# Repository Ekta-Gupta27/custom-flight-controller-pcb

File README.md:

# Custom Flight Controller PCB

A custom-designed flight controller PCB developed for embedded flight-control applications, integrating a high-performance STM32 MCU, multiple inertial and pressure sensors, CAN communication, external flash memory, power management, and dedicated FMU/IO interfaces.

The PCB and schematic were designed using **KiCad 9.0.7**.

---

## 📌 Project Overview

This project focuses on the design and development of a custom flight controller PCB with dedicated interfaces for sensors, communication peripherals, power, debugging, telemetry, PWM outputs, and RC input/output.

The design is divided into multiple functional sections:

- Main Flight Management Unit (FMU)
- IO controller
- IMU and pressure sensing
- CAN communication
- USB connectivity
- External SPI flash memory
- Power regulation
- Telemetry interfaces
- PWM and RC interfaces
- Debug/programming interfaces

---

## ✨ Key Features

- Custom PCB designed from schematic to board layout
- STM32F765VITx main flight controller MCU
- STM32F103CBTx dedicated IO controller
- Multiple onboard sensors
- CAN communication interface
- USB OTG interface
- External SPI flash memory
- Multiple UART interfaces
- I2C and SPI interfaces
- PWM output interface
- SBUS and PPM interfaces
- Debug/programming interface
- Dedicated GPS and telemetry connectors
- Onboard status/safety LEDs
- 3.3 V and 5 V power domains
- Multi-layer PCB layout
- Manufacturing-ready Gerber and drill files

---

## 🧠 Hardware Architecture

### Main Flight Controller

The primary processing unit is an **STM32F765VITx**.

The MCU provides the main processing and peripheral interfaces for the flight-control system, including:

- SPI
- I2C
- UART
- CAN
- Timer/PWM channels
- SWD debugging
- External GPIO

### IO Controller

A dedicated **STM32F103CBTx** is used for the IO section of the design.

The IO controller provides interfaces for:

- SBUS
- PPM
- PWM
- RC input/output
- Safety signals
- Status LEDs
- Debugging
- Additional UART interfaces

---

## 📡 Sensors

The design incorporates multiple sensors:

### ICM-42688-P

6-axis inertial measurement sensor connected through SPI.

### BMI270

6-axis inertial sensor with dedicated interrupt and SPI connections.

### ICP-20100

Pressure sensor connected through the I2C interface.

### BMM150

Magnetic sensor connected through the I2C interface.

---

## 🔌 Communication Interfaces

### CAN

CAN communication is implemented using the **SN65HVD230** transceiver with dedicated CANH and CANL connections and protection circuitry.

### USB

A USB OTG interface is provided along with USB ESD protection using **USBLC6-2P6**.

### UART / Telemetry

Dedicated connectors are provided for:

- TELEM1
- TELEM2
- TELEM3
- UART/I2C interface
- GPS
- FMU communication

### I2C

Multiple I2C buses are available for sensor and peripheral communication.

### SPI

Multiple SPI buses are routed to sensors, flash memory, and external interfaces.

---

## 💾 External Flash Memory

The board includes external SPI flash memory:

**W25Q128JVS**

The flash device is connected to the main MCU through SPI with a dedicated chip-select signal.

---

## ⚡ Power Management

The PCB contains dedicated power regulation and filtering circuitry for the different system power domains.

The design includes:

- 5 V input
- 3.3 V regulation
- USB 5 V input
- External 3.3 V supply
- Decoupling capacitors
- Ferrite filtering
- Power indication circuitry

The schematic includes regulators such as:

- LM1117DT-3.3
- TLV75733PDBVR

---

## 🎛️ Interfaces & Connectors

| Interface | Purpose |
|---|---|
| GPS_PORT | GPS connectivity |
| POWER | Power input |
| TELEM1 | Telemetry |
| TELEM2 | Telemetry |
| TELEM3 | Telemetry |
| CAN_CONN | CAN communication |
| USB_OTG | USB connectivity |
| DEBUG | Debug/programming |
| SPI_PORT | External SPI interface |
| I2C_PORT | External I2C interface |
| UART_I2CB | UART/I2C interface |
| FMU_PWM | PWM outputs |
| IO_PWM | IO PWM interface |
| SBUS_PORT | SBUS interface |
| SBUS_IN | SBUS input |
| PPM_PORT | PPM input |
| IO_DEBUG | IO debugging |

---

# 🖥️ PCB Design

## 3D View – Top

## 3D View – Bottom

## PCB Layout

---

# 📐 Schematic

The complete schematic is provided as a multi-page KiCad schematic covering:

1. FMU / MCU power and peripherals
2. USB and CAN
3. IMU and sensor interfaces
4. IO controller
5. Safety, RC and PWM interfaces

The PDF version is available in:

`docs/schematic.pdf`

---

# 🏭 Manufacturing Files

The `gerbers/` directory contains the manufacturing outputs generated from KiCad, including:

- Front and back copper
- Inner copper layers
- Front and back solder mask
- Front and back silkscreen
- Paste layers
- Board outline
- Drill files
- Gerber job file

These files can be supplied to a PCB manufacturer for fabrication.

---

# 📦 Bill of Materials

A Bill of Materials generated from the KiCad schematic is included in:

`manufacturing/BOM.csv`

The BOM contains information such as:

- Reference designators
- Component quantity
- Component value
- PCB footprint
- Datasheet information
- BOM exclusion fields

---

# 📁 Repository Structure

```text
Custom-FC-RAT/
│
├── README.md
├── custom_fc_rat.kicad_pro
│
├── schematic/
│   └── custom_fc_rat.kicad_sch
│
├── pcb/
│   └── custom_fc_rat.kicad_pcb
│
├── gerbers/
│   ├── *.gbl
│   ├── *.gtl
│   ├── *.gbs
│   ├── *.gts
│   ├── *.gbo
│   ├── *.gto
│   ├── *.gm1
│   ├── *.g1
│   ├── *.g2
│   ├── *.g3
│   ├── *.g4
│   ├── *.drl
│   └── *.gbrjob
│
├── manufacturing/
│   └── BOM.csv
│
├── images/
│   ├── pcb_3d_top.png
│   ├── pcb_3d_bottom.png
│   └── pcb_layout.png
│
└── docs/
    └── schematic.pdf
```

---

# 🛠️ Design Tools

| Tool | Purpose |
|---|---|
| KiCad 9.0.7 | Schematic & PCB design |
| KiCad 3D Viewer | PCB visualization |
| KiCad Gerber Generator | Manufacturing file generation |

---

# 🚀 Future Improvements

Possible future development includes:

- Hardware validation and bring-up documentation
- Flight-controller firmware integration
- Sensor calibration and validation
- Power integrity testing
- Communication interface testing
- EMI/EMC validation
- Flight testing
- PCB revisions based on hardware testing

---

# 📄 Documentation

The editable KiCad design files and schematic PDF are included so that the hardware design can be inspected and further developed.

---

# 👩‍💻 Author

**Ekta Gupta**

Custom PCB / Flight Controller Design Project

---

## ⭐ Project Status

**Hardware Design Completed**

Schematic, PCB layout, 3D visualization, BOM, and manufacturing files are included in this repository.

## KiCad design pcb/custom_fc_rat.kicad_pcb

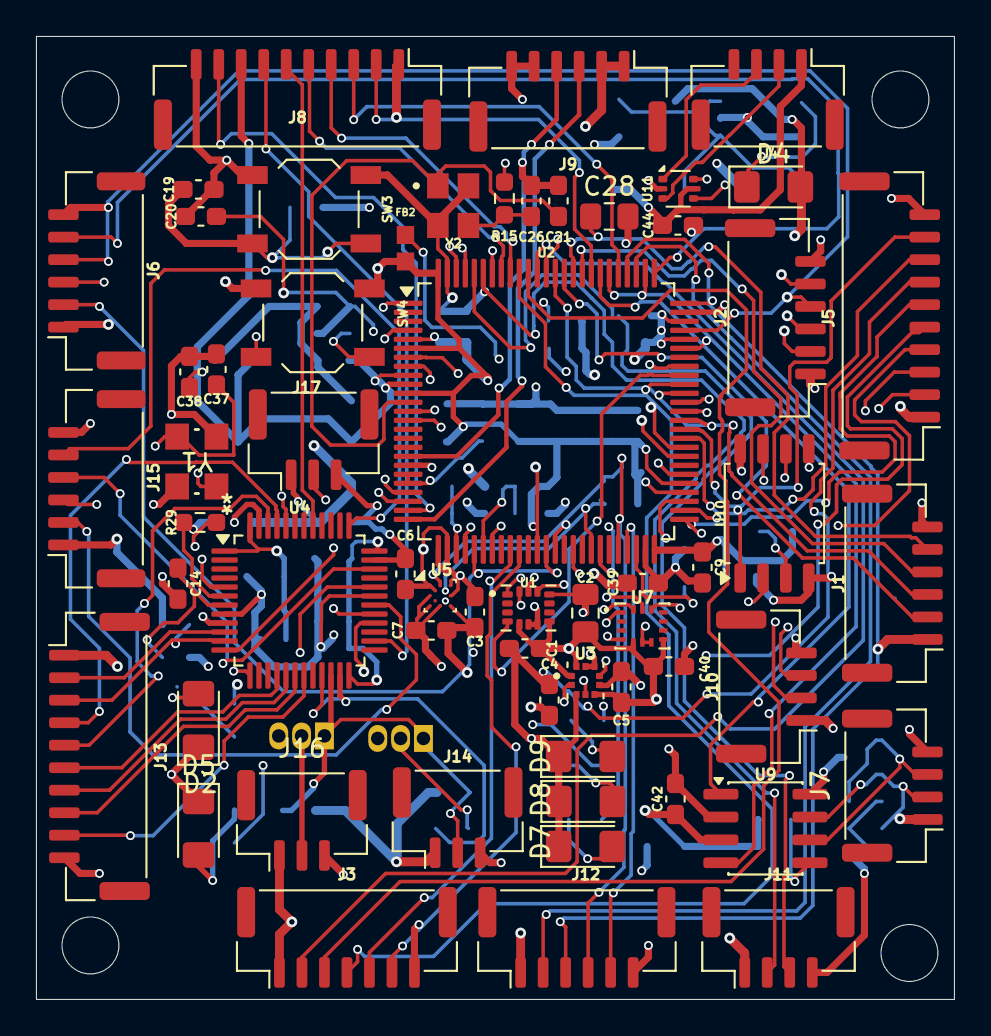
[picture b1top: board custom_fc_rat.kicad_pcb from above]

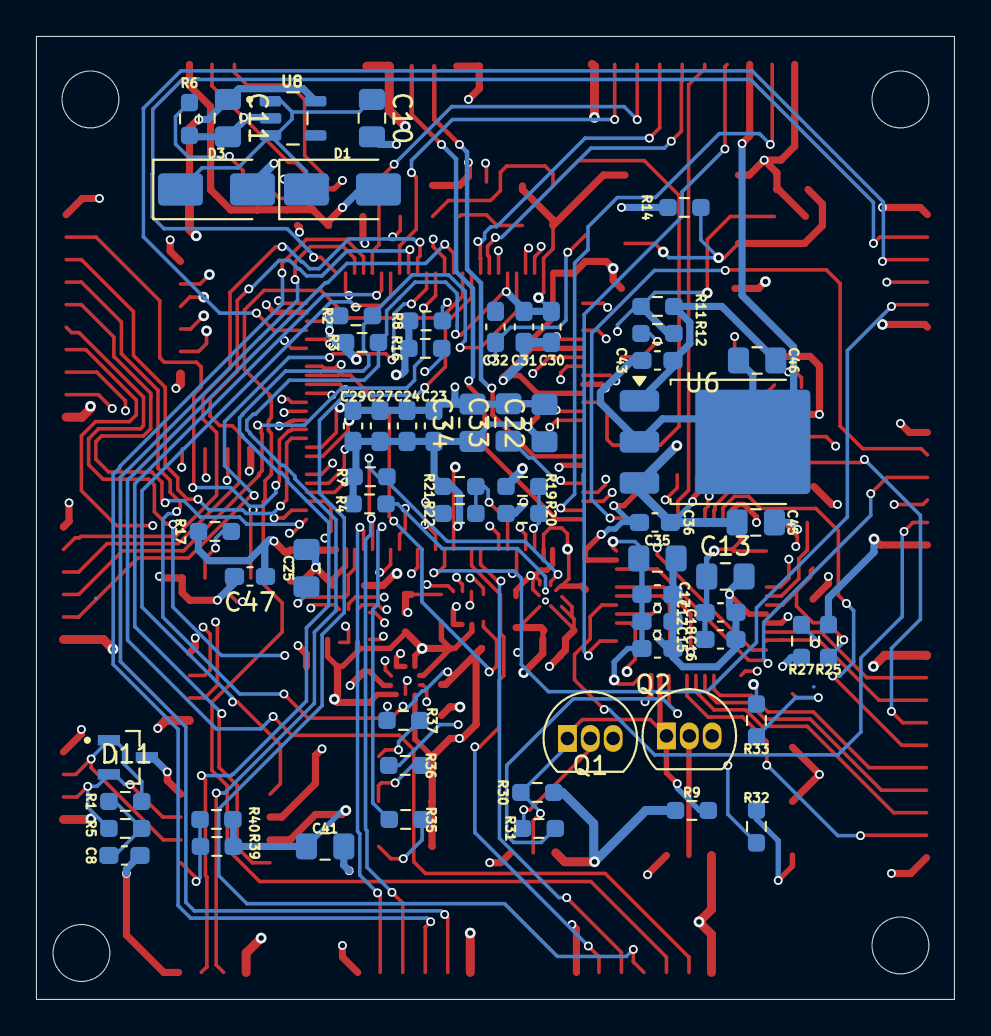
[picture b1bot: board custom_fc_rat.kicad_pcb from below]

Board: 6 copper layers, 51.0 x 53.5 mm, 122 parts (63 on the bottom side), 121 nets.

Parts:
C1, C4, C5, C6, C7, C9, C12, C14, C15, C16, C17, C18, C19, C20, C23, C24, C27, C29, C30, C31, C32, C36, C39, C40, C42, C43, C44: 0.1u; C_0603_1608Metric_Pad1.08x0.95mm_HandSolder
C2, C10, C11: 2.2u; C_0805_2012Metric_Pad1.18x1.45mm_HandSolder
C3: 10n; C_0603_1608Metric_Pad1.08x0.95mm_HandSolder
C8: 4.7n; C_0603_1608Metric_Pad1.08x0.95mm_HandSolder
C13, C33, C34, C41: 1u; C_0805_2012Metric_Pad1.18x1.45mm_HandSolder
C21, C26: 8pF; C_0603_1608Metric_Pad1.08x0.95mm_HandSolder
C22, C35, C45, C46: 10u; C_0805_2012Metric_Pad1.18x1.45mm_HandSolder
C25, C28: 2u2; C_0805_2012Metric_Pad1.18x1.45mm_HandSolder
C37, C38: 18pF; C_0603_1608Metric_Pad1.08x0.95mm_HandSolder
C47: 1u; C_0603_1608Metric_Pad1.08x0.95mm_HandSolder
D1, D3: SS34; D_SMA
D2, D4, D5, D7, D8, D9: LED; LED_1206_3216Metric_Pad1.42x1.75mm_HandSolder
D11: ESD2CANFD24DBZRQ1; SOT95P237X112-3N
FB2: FerriteBead; BEADC1608X95N
J1: TELEM1; JST_GH_BM06B-GHS-TBT_1x06-1MP_P1.25mm_Vertical
J2: TELEM2; JST_GH_BM06B-GHS-TBT_1x06-1MP_P1.25mm_Vertical
J3: SPI_PORT; JST_GH_BM07B-GHS-TBT_1x07-1MP_P1.25mm_Vertical
J4: USB_OTG; JST_GH_BM04B-GHS-TBT_1x04-1MP_P1.25mm_Vertical
J5: FMU_PWM; JST_GH_BM10B-GHS-TBT_1x10-1MP_P1.25mm_Vertical
J6: DEBUG; JST_GH_SM06B-GHS-TB_1x06-1MP_P1.25mm_Horizontal
J7: CAN_CONN; JST_GH_BM04B-GHS-TBT_1x04-1MP_P1.25mm_Vertical
J8: GPS_PORT; JST_GH_BM10B-GHS-TBT_1x10-1MP_P1.25mm_Vertical
J9: POWER; JST_GH_BM06B-GHS-TBT_1x06-1MP_P1.25mm_Vertical
J10: TELEM3; JST_GH_BM04B-GHS-TBT_1x04-1MP_P1.25mm_Vertical
J11: I2C_PORT; JST_GH_BM04B-GHS-TBT_1x04-1MP_P1.25mm_Vertical
J12: UART_I2CB; JST_GH_BM06B-GHS-TBT_1x06-1MP_P1.25mm_Vertical
J13: IO_PWM; JST_GH_BM10B-GHS-TBT_1x10-1MP_P1.25mm_Vertical
J14: SBUS_PORT; JST_GH_BM03B-GHS-TBT_1x03-1MP_P1.25mm_Vertical
J15: IO_DEBUG; JST_GH_SM06B-GHS-TB_1x06-1MP_P1.25mm_Horizontal
J16: SBUS_IN; JST_GH_BM03B-GHS-TBT_1x03-1MP_P1.25mm_Vertical
J17: PPM_PORT; JST_GH_BM03B-GHS-TBT_1x03-1MP_P1.25mm_Vertical
Q1, Q2: BC547; TO-92_Inline
R1, R5: 60R; R_0603_1608Metric_Pad0.98x0.95mm_HandSolder
R2, R3, R4, R7, R8, R16, R39, R40: 4K7; R_0603_1608Metric_Pad0.98x0.95mm_HandSolder
R6: 1k5; R_0603_1608Metric_Pad0.98x0.95mm_HandSolder
R9, R30: 10k; R_0603_1608Metric_Pad0.98x0.95mm_HandSolder
R11, R14, R17, R25, R27: 10K; R_0603_1608Metric_Pad0.98x0.95mm_HandSolder
R12: 22R; R_0603_1608Metric_Pad0.98x0.95mm_HandSolder
R15: 47R; R_0603_1608Metric_Pad0.98x0.95mm_HandSolder
R19, R20, R21, R22: 5K1; R_0603_1608Metric_Pad0.98x0.95mm_HandSolder
R29: 150R; R_0603_1608Metric_Pad0.98x0.95mm_HandSolder
R31: 4.7k; R_0603_1608Metric_Pad0.98x0.95mm_HandSolder
R32, R33, R35, R36, R37: 220R; R_0603_1608Metric_Pad0.98x0.95mm_HandSolder
SW3, SW4: SW_Push; SW_SPST_TL3342
U1: ICM-42688-P; PQFN50P300X250X97-14N
U2: STM32F765VITx; LQFP-100_14x14mm_P0.5mm
U3: ICP-20100; PQFN50P200X200X85-10N
U4: STM32F103CBTx; LQFP-48_7x7mm_P0.5mm
U5: BMM150; WLCSP-12_1.56x1.56mm_P0.4mm
U6: LM1117DT-3.3; TO-252-3_TabPin2
U7: BMI270; XDCR_BMI270
U8: TLV75733PDBVR; SOT95P280X145-5N
U9: SN65HVD230; SOIC-8_3.9x4.9mm_P1.27mm
U10: W25Q128JVS; SOIC-8_5.3x5.3mm_P1.27mm
U11: USBLC6-2P6; SOT-666
Y1: Crystal_GND24; YSX321SL_YXC
Y2: Crystal_GND24; OSC_X322516MLB4SI

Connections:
+3.3V: C1.1, C2.1, C3.1, C4.1, C5.1, C6.1, C7.1, C9.1, C11.1, C12.1, C13.1, C15.1, C16.1, C17.1, C18.1, C22.1, C23.1, C24.1, C27.1, C29.1, C30.1, C31.1, C34.1, C35.1, C39.1, C40.1, C41.1, C42.1, C47.1, D4.2 (A), FB2.2, J6.1, J15.1, R2.1, R3.1, R4.1, R7.1, R8.1, R14.1, R16.1, R17.1, R21.2, R25.1, R39.1, R40.1, SW4.1, U1.5 (VDDIO), U1.8 (VDD), U2.6 (VBAT), U2.11 (VDD), U2.27 (VDD), U2.50 (VDD), U2.75 (VDD), U2.100 (VDD), U3.1 (CSB), U3.5 (VDD), U3.10 (VDDIO), U4.1 (VBAT), U4.9 (VDDA), U4.24 (VDD), U4.36 (VDD), U4.48 (VDD), U5.A1 (PS), U5.B2 (VDDIO), U5.E5 (VDD), U7.5 (VDDIO), U7.8 (VDD), U8.5 (OUT), U9.3 (VCC), U10.8 (VCC)
+5V: C36.2, C45.1, D3.2 (A), J1.1, J2.1, J3.1, J5.1, J7.1, J8.1, J9.1, J9.2, J10.1, J11.1, J12.1, J13.1, J14.1, J16.1, J17.1, R9.1, R19.2, R30.1, U6.3 (VI)
/IMU/DRDY1_ICM42688: U1.4 (INT1/INT), U2.67 (PA8)
/IMU/DRDY2_BMM150: U2.66 (PC9), U5.D4 (DRDY)
/IMU/DRDY4_ICP20100: U2.62 (PD15), U3.7 (INT)
/IMU/ICM42688_CS: U1.12 (AP_CS), U2.51 (PB12)
/IMU/SPI1_MISO: U1.1 (AP_SDO/AP_AD0), U2.30 (PA6)
/IMU/SPI1_MOSI: U1.14 (AP_SDA/AP_SDIO/AP_SDI), U2.88 (PD7)
/IMU/SPI1_SCK: U1.13 (AP_SCL/AP_SCLK), U2.29 (PA5)
/IO_FMU/AMBER_LED: R33.1, U4.28 (PB15)
/IO_FMU/D_BOOBT0_R: R27.1, U4.44 (BOOT0)
/IO_FMU/RCIN: J17.2, U4.29 (PA8)
/IO_FMU/RING_LED: R32.1, U4.32 (PA11)
/IO_FMU/SAFETY_INPUT: J8.6, U4.41 (PB5)
/IO_FMU/SAFETY_LED: J8.7, U4.26 (PB13)
/IO_FMU/SWDCLK: J15.5, U4.37 (PA14)
/IO_FMU/SWDIO: J15.4, U4.34 (PA13)
/IO_FMU/TIM2_CH1: J13.2, U4.10 (PA0)
/IO_FMU/TIM2_CH2: J13.3, U4.11 (PA1)
/IO_FMU/TIM3_CH1: J13.6, U4.16 (PA6)
/IO_FMU/TIM3_CH2: J13.7, U4.17 (PA7)
/IO_FMU/TIM3_CH3: J13.8, U4.18 (PB0)
/IO_FMU/TIM3_CH4: J13.9, U4.19 (PB1)
/IO_FMU/TIM4_CH3: J13.4, U4.45 (PB8)
/IO_FMU/TIM4_CH4: J13.5, U4.46 (PB9)
/IO_FMU/USART1_RX: J15.3, U4.31 (PA10)
/IO_FMU/USART1_TX: J15.2, U4.30 (PA9)
/IO_FMU/USART2_RX: U2.98 (PE1), U4.13 (PA3)
/IO_FMU/USART2_TX: U2.97 (PE0), U4.12 (PA2)
/IO_FMU/USART3_RX: J14.2, Q1.1 (C), Q2.1 (C), R9.2, R30.2, U4.22 (PB11)
/IO_FMU/USART3_TX: R31.1, U4.21 (PB10)
/fmu_mcu_power/3V3_EXTERNAL: C43.1, C46.1, J8.8, U6.2 (VO)
/fmu_mcu_power/5V_USB: C44.1, D1.2 (A), J4.1 (VBUS), U2.68 (PA9), U11.5 (VBUS)
/fmu_mcu_power/BATT_CURRENT_SENS: J9.3, U2.25 (PA3)
/fmu_mcu_power/BATT_VOLTAGE_SENS: J9.4, U2.18 (PC3)
/fmu_mcu_power/BMI270_CS: U2.32 (PC4), U7.12 (CSB)
/fmu_mcu_power/CAN1_RX: U2.81 (PD0), U9.4 (R)
/fmu_mcu_power/CAN1_TX: U2.82 (PD1), U9.1 (D)
/fmu_mcu_power/DRDY3_BMI270: U2.65 (PC8), U7.4 (INT1)
/fmu_mcu_power/D_BOOBT0_R: C20.1, R11.1, R12.2, U2.94 (BOOT0)
/fmu_mcu_power/D_NRST: C19.2, R14.2, SW3.2, U2.14 (NRST), U10.7 (~HOLD/~RESET/IO_{3})
/fmu_mcu_power/EXTERNAL_CS1: J3.5, U2.34 (PB0)
/fmu_mcu_power/EXTERNAL_CS2: J3.6, U2.35 (PB1)
/fmu_mcu_power/FLASH_CS: U2.77 (PA15), U10.1 (~CS)
/fmu_mcu_power/GPIO_LED_BLUE: R36.1, U2.8 (PC14)
/fmu_mcu_power/GPIO_LED_GREEN: R35.1, U2.7 (PC13)
/fmu_mcu_power/GPIO_LED_RED: R37.1, U2.9 (PC15)
/fmu_mcu_power/I2C1_SCL: J8.4, R16.2, U2.92 (PB6), U3.2 (SCL)
/fmu_mcu_power/I2C1_SDA: J8.5, R8.2, U2.93 (PB7), U3.4 (SDA/SDIO/SDI)
/fmu_mcu_power/I2C2_SCL: J12.4, R7.2, U2.46 (PB10), U5.A3 (SCK)
/fmu_mcu_power/I2C2_SDA: J12.5, R4.2, U2.47 (PB11), U5.B4 (SDI)
/fmu_mcu_power/I2C4_SCL: J11.2, R3.2, U2.95 (PB8)
/fmu_mcu_power/I2C4_SDA: J11.3, R2.2, U2.96 (PB9)
/fmu_mcu_power/SCALED_V3V3: R21.1, R22.1, U2.31 (PA7)
/fmu_mcu_power/SPI2_MISO: U2.53 (PB14), U10.2 (DO/IO_{1})
/fmu_mcu_power/SPI2_MOSI: U2.54 (PB15), U10.5 (DI/IO_{0})
/fmu_mcu_power/SPI2_SCK: U2.52 (PB13), U10.6 (CLK)
/fmu_mcu_power/SPI3_MISO: J3.3, U2.90 (PB4)
/fmu_mcu_power/SPI3_MOSI: J3.4, U2.91 (PB5)
/fmu_mcu_power/SPI3_SCK: J3.2, U2.89 (PB3)
/fmu_mcu_power/SPI4_MISO: U2.4 (PE5), U7.1 (SDO)
/fmu_mcu_power/SPI4_MOSI: U2.5 (PE6), U7.14 (SDX)
/fmu_mcu_power/SPI4_SCK: U2.1 (PE2), U7.13 (SCX)
/fmu_mcu_power/SWDCLK: J6.5, U2.76 (PA14)
/fmu_mcu_power/SWDIO: J6.4, U2.72 (PA13)
/fmu_mcu_power/TIM1_CH1: J5.2, U2.39 (PE9)
/fmu_mcu_power/TIM1_CH2: J5.3, U2.41 (PE11)
/fmu_mcu_power/TIM1_CH3: J5.4, U2.43 (PE13)
/fmu_mcu_power/TIM1_CH4: J5.5, U2.44 (PE14)
/fmu_mcu_power/TIM2_CH1: J5.6, U2.22 (PA0)
/fmu_mcu_power/TIM2_CH2: J5.7, U2.23 (PA1)
/fmu_mcu_power/TIM2_CH3: J8.9, U2.24 (PA2)
/fmu_mcu_power/TIM4_CH2: J5.8, U2.60 (PD13)
/fmu_mcu_power/TIM4_CH3: J5.9, U2.61 (PD14)
/fmu_mcu_power/UART4_RX: J12.3, U2.79 (PC11)
/fmu_mcu_power/UART4_TX: J12.2, U2.78 (PC10)
/fmu_mcu_power/UART5_RX: J8.3, U2.80 (PC12)
/fmu_mcu_power/UART5_TX: J8.2, U2.83 (PD2)
/fmu_mcu_power/UART7_RX: J6.3, U2.37 (PE7)
/fmu_mcu_power/UART7_TX: J6.2, U2.38 (PE8)
/fmu_mcu_power/USART2_CTS: J1.4, U2.84 (PD3)
/fmu_mcu_power/USART2_RTS: J1.5, U2.85 (PD4)
/fmu_mcu_power/USART2_RX: J1.3, U2.87 (PD6)
/fmu_mcu_power/USART2_TX: J1.2, U2.86 (PD5)
/fmu_mcu_power/USART3_CTS: J2.4, U2.58 (PD11)
/fmu_mcu_power/USART3_RTS: J2.5, U2.59 (PD12)
/fmu_mcu_power/USART3_RX: J2.3, U2.56 (PD9)
/fmu_mcu_power/USART3_TX: J2.2, U2.55 (PD8)
/fmu_mcu_power/USART6_RX: J10.3, U2.64 (PC7)
/fmu_mcu_power/USART6_TX: J10.2, U2.63 (PC6)
/fmu_mcu_power/USB_D+: J4.3 (D+), U11.1 (I/O1)
/fmu_mcu_power/USB_D-: J4.2 (D-), U11.3 (I/O2)
/fmu_mcu_power/USB_DM: U2.70 (PA11), U11.4 (I/O2)
/fmu_mcu_power/USB_DP: U2.71 (PA12), U11.6 (I/O1)
/fmu_mcu_power/VDDA: C32.1, C33.1, FB2.1, U2.20 (VREF+), U2.21 (VDDA)
/fmu_mcu_power/VDD_5V_SENS: R19.1, R20.1, U2.28 (PA4)
GND: C1.2, C2.2, C3.2, C4.2, C5.2, C6.2, C7.2, C8.2, C9.2, C10.2, C11.2, C12.2, C13.2, C14.1, C15.2, C16.2, C17.2, C18.2, C19.1, C20.2, C21.2, C22.2, C23.2, C24.2, C25.2, C26.2, C27.2, C28.2, C29.2, C30.2, C31.2, C32.2, C33.2, C34.2, C35.2, C36.1, C37.2, C38.2, C39.2, C40.2, C41.2, C42.2, C43.2, C44.2, C45.2, C46.2, C47.2, D2.1 (K), D5.1 (K), D7.1 (K), D8.1 (K), D9.1 (K), D11.3, J1.6, J2.6, J3.7, J5.10, J6.6, J7.4, J8.10, J9.5, J9.6, J10.4, J11.4, J12.6, J13.10, J14.3, J15.6, J16.3, J17.3, Q1.3 (E), Q2.3 (E), R6.2, R11.2, R20.2, R22.2, R27.2, SW3.1, U1.6 (GND), U1.7 (RESV_7), U1.11 (RESV_11), U2.10 (VSS), U2.19 (VSSA), U2.26 (VSS), U2.49 (VSS), U2.74 (VSS), U2.99 (VSS), U3.3 (VSS), U3.6 (SDO/AD0), U3.8 (RESV), U3.9 (RESV), U4.8 (VSSA), U4.23 (VSS), U4.35 (VSS), U4.47 (VSS), U5.A5 (CSB), U5.C1 (SDO), U5.C5 (GND), U5.E1 (GND), U5.E3 (GND), U6.1 (GND), U7.6 (GNDIO), U7.7 (GND), U8.2 (GND), U9.2 (GND), U9.8 (Rs), U10.4 (GND), U11.2 (GND), Y1.2 (G), Y1.4 (G), Y2.2 (G), Y2.4 (G)
unnamed: C8.1, R1.1, R5.2
unnamed: C26.1, R15.1, Y2.3
unnamed: C37.1, R29.1, Y1.3
unnamed: C10.1, D1.1 (K), D3.1 (K), U8.1 (IN), U8.3 (EN)
unnamed: D2.2 (A), R32.2
unnamed: D4.1 (K), R6.1
unnamed: D5.2 (A), R33.2
unnamed: D7.2 (A), R35.2
unnamed: D8.2 (A), R36.2
unnamed: D9.2 (A), R37.2
unnamed: D11.2, J7.2, R5.1, U9.7 (CANH)
unnamed: D11.1, J7.3, R1.2, U9.6 (CANL)
unnamed: J16.2, Q2.2 (B)
unnamed: Q1.2 (B), R31.2
unnamed: R12.1, SW4.2
unnamed: C21.1, U2.12 (PH0), Y2.1
unnamed: R15.2, U2.13 (PH1)
unnamed: C25.1, U2.48 (VCAP_1)
unnamed: C28.1, U2.73 (VCAP_2)
unnamed: C14.2, R25.2, U4.7 (NRST)
unnamed: C38.1, U4.5 (PD0), Y1.1
unnamed: R29.2, U4.6 (PD1)
unnamed: R39.2, R40.2, U9.5 (Vref)
unnamed: R17.2, U10.3 (~WP/IO_{2})
